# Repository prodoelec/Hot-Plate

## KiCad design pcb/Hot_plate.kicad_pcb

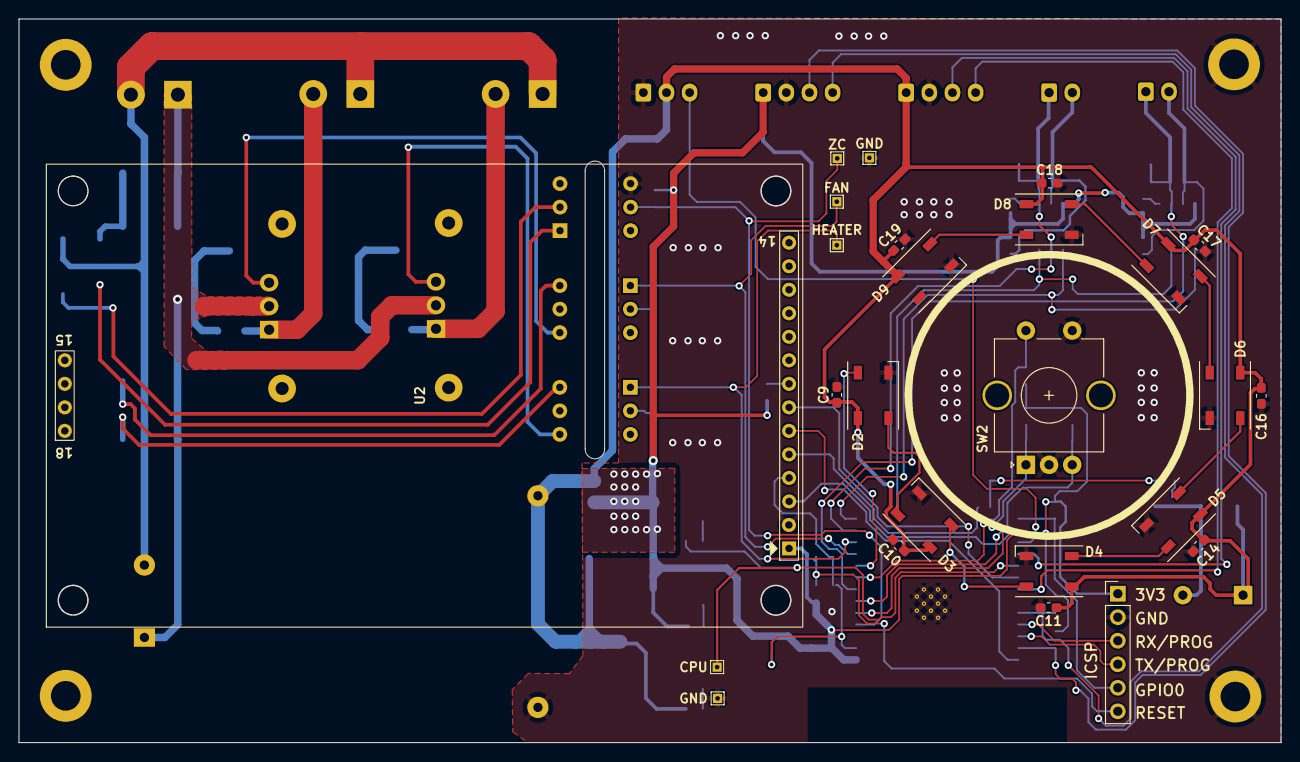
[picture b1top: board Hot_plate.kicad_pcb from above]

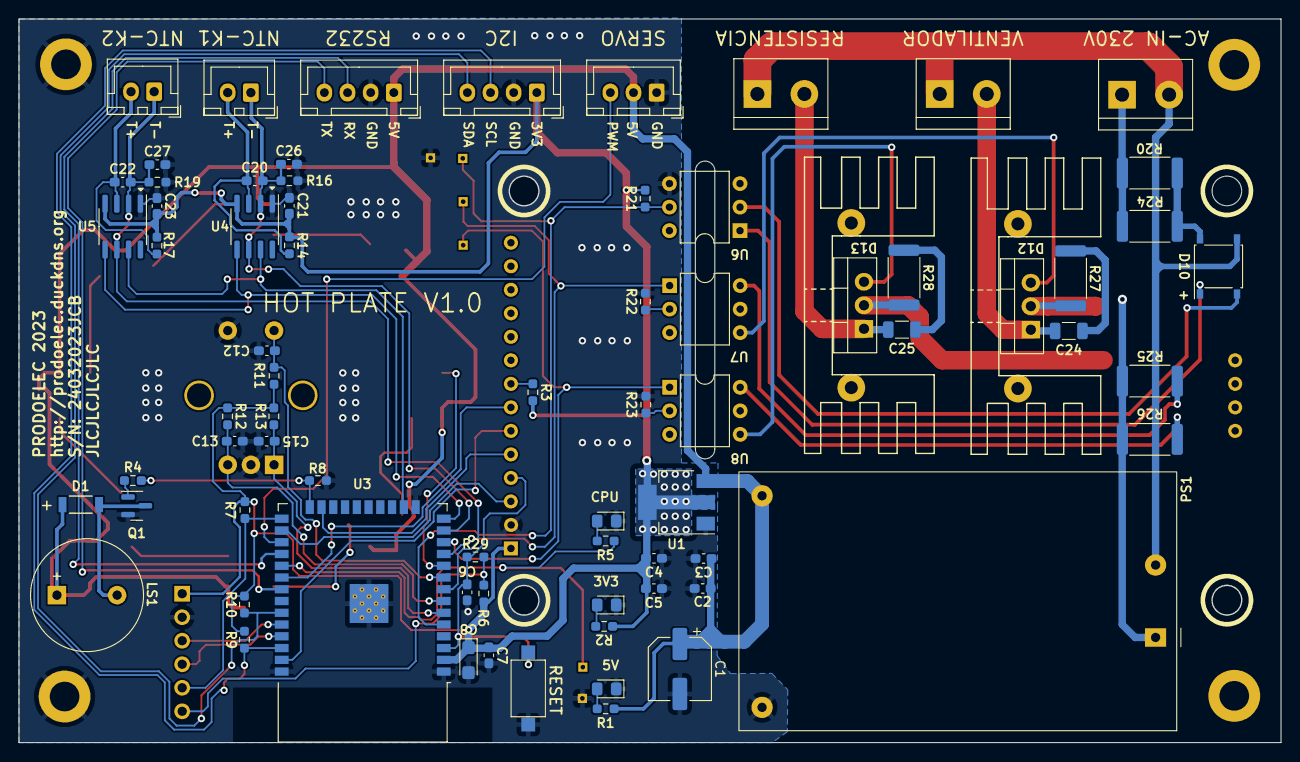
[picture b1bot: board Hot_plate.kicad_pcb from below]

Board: 2 copper layers, 136.3 x 78.1 mm, 103 parts (74 on the bottom side), 60 nets.

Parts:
C1: 220uF/16V; CP_Elec_6.3x7.7
C2, C5: 100nF/25V; C_0603_1608Metric_Pad1.08x0.95mm_HandSolder
C3, C4: 10uF/25V; C_0603_1608Metric_Pad1.08x0.95mm_HandSolder
C6, C7, C9, C10, C11, C12, C13, C14, C15, C16, C17, C18, C19, C20, C21, C22, C23, C26, C27: 100nF; C_0603_1608Metric_Pad1.08x0.95mm_HandSolder
C8: 100uF/10V; CP_EIA-3216-10_Kemet-I
C24, C25: 10nF/400V; C_1206_3216Metric
D1: BAS85-115; DIODE_BAS85_115-M
D2, D3, D4, D5, D6, D7, D8, D9: WS2812B; LED_WS2812B_PLCC4_5.0x5.0mm_P3.2mm
D10: ABS8; Diode_Bridge_Diotec_ABS
D12, D13: BTB10-800CWRG; TO-220-3_Vertical
H1, H3: MountingHole; MountingHole_3.2mm_M3_DIN965_Pad
H2, H4: MountingHole_Pad; MountingHole_3.2mm_M3_DIN965_Pad
HS1, HS2: Heatsink_Pad; Heatsink_Stonecold_HS-132_32x14mm_2xFixation1.5mm
J1: IN-AC; TerminalBlock_bornier-2_P5.08mm
J2: ISCP; PinHeader_1x06_P2.54mm_Vertical
J3: PANTALLA NEXTION; JST_XH_B4B-XH-A_1x04_P2.50mm_Vertical
J4: SERVO; JST_XH_B3B-XH-A_1x03_P2.50mm_Vertical
J5: I2C; JST_XH_B4B-XH-A_1x04_P2.50mm_Vertical
J6: SONDA 1; JST_XH_B2B-XH-A_1x02_P2.50mm_Vertical
J7: SONDA 2; JST_XH_B2B-XH-A_1x02_P2.50mm_Vertical
J8: VENTILADOR; TerminalBlock_bornier-2_P5.08mm
J9: RESISTENCIA; TerminalBlock_bornier-2_P5.08mm
LD1: 5V; LED_0805_2012Metric_Pad1.15x1.40mm_HandSolder
LD2: 3V3; LED_0805_2012Metric_Pad1.15x1.40mm_HandSolder
LD3: CPU; LED_0805_2012Metric_Pad1.15x1.40mm_HandSolder
LS1: PKMCS0909E4000-R1; Buzzer_12x9.5RM6.5
PS1: HLK-10M05; Converter_ACDC_HiLink_HLK-10Mxx
Q1: BC847; SOT-23
R1: 4K7; R_0603_1608Metric_Pad0.98x0.95mm_HandSolder
R2, R5, R29: 470; R_0603_1608Metric_Pad0.98x0.95mm_HandSolder
R3: 0; R_0603_1608Metric_Pad0.98x0.95mm_HandSolder
R4: 1K; R_0603_1608Metric_Pad0.98x0.95mm_HandSolder
R6, R7, R8, R9, R10, R11, R12, R13, R21: 10K; R_0603_1608Metric_Pad0.98x0.95mm_HandSolder
R14, R17: 0 *; R_0603_1608Metric_Pad0.98x0.95mm_HandSolder
R16, R19: 100K; R_0603_1608Metric_Pad0.98x0.95mm_HandSolder
R20, R24: 120K; R_2512_6332Metric
R22, R23: 220; R_0603_1608Metric_Pad0.98x0.95mm_HandSolder
R25, R26: 1K; R_2512_6332Metric
R27, R28: 39 *; R_2512_6332Metric
SW1: RESET; SW_SPST_CK_RS282G05A3
SW2: RotaryEncoder_Switch; RotaryEncoder_Alps_EC11E-Switch_Vertical_H20mm_CircularMoun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
TP1: HEATER; TestPoint_THTPad_1.0x1.0mm_Drill0.5mm
TP2: FAN; TestPoint_THTPad_1.0x1.0mm_Drill0.5mm
TP3: ZC; TestPoint_THTPad_1.0x1.0mm_Drill0.5mm
TP4, TP6: GND; TestPoint_THTPad_1.0x1.0mm_Drill0.5mm
TP5: CPU; TestPoint_THTPad_1.0x1.0mm_Drill0.5mm
U1: LD1117S33TR_SOT223; SOT-223-3_TabPin2
U2: ILI9341
U3: ESP32-WROOM-32
U4, U5: MAX6675; SOIC-8_3.9x4.9mm_P1.27mm
U6: 4N25; DIP-6_W7.62mm
U7, U8: MOC3021M; DIP-6_W7.62mm

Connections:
+3V3: C4.1, C5.1, C7.1, C8.1, C21.2, C23.2, J2.1, J5.1, R2.1, R3.2, R6.1, R7.2, R9.2, R10.2, R11.2, R12.2, R13.2, R14.2, R17.2, R21.2, U1.2 (VO), U2.1 (3V3), U3.2 (VDD), U4.4 (VCC), U5.4 (VCC)
+5V: C1.1, C2.1, C3.1, C9.1, C10.1, C11.1, C14.1, C16.1, C17.1, C18.1, C19.1, D1.1 (K), D2.1 (VDD), D3.1 (VDD), D4.1 (VDD), D5.1 (VDD), D6.1 (VDD), D7.1 (VDD), D8.1 (VDD), D9.1 (VDD), J3.1, J4.2, LS1.1, PS1.4 (+Vout), R1.1, U1.3 (VI)
BUZZER: R4.2, R8.2, U3.24 (IO2)
CK_ENC: C13.1, R12.1, SW2.B, U3.7 (IO35)
DT_ENC: C15.1, R13.1, SW2.A, U3.6 (IO34)
GND: C1.2, C2.2, C3.2, C4.2, C5.2, C6.2, C7.2, C8.2, C9.2, C10.2, C11.2, C12.2, C13.2, C14.2, C15.2, C16.2, C17.2, C18.2, C19.2, C21.1, C23.1, C26.2, C27.2, D2.3 (VSS), D3.3 (VSS), D4.3 (VSS), D5.3 (VSS), D6.3 (VSS), D7.3 (VSS), D8.3 (VSS), D9.3 (VSS), H2.1, H4.1, J2.2, J3.2, J4.1, J5.2, LD1.1 (K), LD2.1 (K), LD3.1 (K), PS1.3 (-Vout), Q1.2 (E), R8.1, R16.1, R19.1, R22.1, R23.1, SW1.1, SW2.C, SW2.S1, TP4.1, TP6.1, U1.1 (GND), U2.2 (GND), U3.1 (GND), U3.15 (GND), U3.38 (GND), U3.39 (GND), U4.1 (GND), U5.1 (GND), U6.4
GPIO0: J2.5, R7.1, U3.25 (IO0)
LED_CPU: R5.1, TP5.1, U3.29 (IO5)
LED_ENC: D2.4 (DIN), U3.10 (IO25)
LINE: D12.2 (A2), D13.2 (A2), J1.1, PS1.1 (AC/L), R20.2, R24.2, R25.2, R26.2, R27.2, R28.2
MAX_CS1/NTC1: C20.2, C26.1, J6.1, R16.2, U3.13 (IO14), U4.2 (T-), U4.6 (~CS)
MAX_CS2/NTC2: C22.2, C27.1, J7.1, R19.2, U3.8 (IO32), U5.2 (T-), U5.6 (~CS)
MAX_SCK: U3.14 (IO12), U4.5 (SCK), U5.5 (SCK)
MAX_SO: U3.16 (IO13), U4.7 (SO), U5.7 (SO)
MOSI: U2.6 (MOSI), U3.37 (IO23)
NEUT: D10.3, J1.2, J8.1, J9.1, PS1.2 (AC/N)
unnamed: C24.1, R27.1
unnamed: C25.1, R28.1
unnamed: D1.2 (A), LS1.2, Q1.3 (C)
unnamed: D2.2 (DOUT), D3.4 (DIN)
unnamed: D3.2 (DOUT), D4.4 (DIN)
unnamed: D4.2 (DOUT), D5.4 (DIN)
unnamed: D5.2 (DOUT), D6.4 (DIN)
unnamed: D6.2 (DOUT), D7.4 (DIN)
unnamed: D7.2 (DOUT), D8.4 (DIN)
unnamed: D8.2 (DOUT), D9.4 (DIN)
unnamed: D10.1 (+), U6.1
unnamed: D10.2 (-), U6.2
unnamed: D10.4, R20.1, R24.1
unnamed: C24.2, D12.1 (A1), J8.2
unnamed: D12.3 (G), U7.4
unnamed: C25.2, D13.1 (A1), J9.2
unnamed: D13.3 (G), U8.4
unnamed: C20.1, J6.2, R14.1, U4.3 (T+)
unnamed: C22.1, J7.2, R17.1, U5.3 (T+)
unnamed: LD1.2 (A), R1.2
unnamed: LD2.2 (A), R2.2
unnamed: LD3.2 (A), R5.2
unnamed: Q1.1 (B), R4.1
unnamed: R22.2, U7.2
unnamed: R23.2, U8.2
unnamed: R25.1, U7.6
unnamed: R26.1, U8.6
unnamed: R3.1, U2.8 (LED)
PWM/SERVO: J4.3, U3.27 (IO16)
RST_ESP: C6.1, R29.2, SW1.2, U2.4 (RESET), U3.3 (EN)
RST_PROG: J2.6, R6.2, R29.1
RX_232: J3.3, U3.28 (IO17)
RX_PROG: J2.3, U3.34 (RXD0/IO3)
SCK: U2.7 (SCK), U3.30 (IO18)
SCL: J5.3, R9.1, U3.36 (IO22)
SDA: J5.4, R10.1, U3.33 (IO21)
SSR_FAN: TP2.1, U3.11 (IO26), U7.1
SSR_HEATER: TP1.1, U3.12 (IO27), U8.1
SW_ENC: C12.1, R11.1, SW2.S2, U3.9 (IO33)
TFT_CS: U2.3 (TFT_CS), U3.26 (IO4)
TFT_DC: U2.5 (TFT_DC), U3.23 (IO15)
TX_232: J3.4, U3.31 (IO19)
TX_PROG: J2.4, U3.35 (TXD0/IO1)
ZERO_C: R21.1, TP3.1, U3.5 (SENSOR_VN), U6.5

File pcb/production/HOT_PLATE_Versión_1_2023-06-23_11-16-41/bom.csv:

Designator,Footprint,Quantity,Value,LCSC Part #
C1,CP_Elec_8x6.9,1,220uF/10V,
"C10, C11, C12, C13, C14, C15, C16, C17, C18, C19, C20, C21, C22, C23, C6, C7, C9",0603,17,100nF,
"C2, C5",0603,2,100nF/25V,
"C24, C25",1206,2,10nF/400V,
"C3, C4",0603,2,10uF/25V,
C8,CP_EIA-3216-10_Kemet-I,1,100uF/10V,
D1,DIODE_BAS85_115-M,1,BAS85-115,
D10,Diode_Bridge_Diotec_ABS,1,ABS8,
"D12, D13",TO-220-3_Vertical,2,BTB10-800CWRG,
"D2, D3, D4, D5, D6, D7, D8, D9",LED_WS2812B_PLCC4_5.0x5.0mm_P3.2mm,8,WS2812B,
"H1, H3",MountingHole_3.2mm_M3_DIN965_Pad,2,MountingHole,
"H2, H4",MountingHole_3.2mm_M3_DIN965_Pad,2,MountingHole_Pad,
"HS1, HS2",Heatsink_Stonecold_HS-132_32x14mm_2xFixation1.5mm,2,Heatsink_Pad,
J1,TerminalBlock_bornier-2_P5.08mm,1,IN-AC,
J2,PinHeader_1x06_P2.54mm_Vertical,1,ISCP,
J3,JST_XH_B4B-XH-A_1x04_P2.50mm_Vertical,1,PANTALLA NEXTION,
J4,JST_XH_B3B-XH-A_1x03_P2.50mm_Vertical,1,SERVO,
J5,JST_XH_B4B-XH-A_1x04_P2.50mm_Vertical,1,I2C,
J6,JST_XH_B2B-XH-A_1x02_P2.50mm_Vertical,1,SONDA 1,
J7,JST_XH_B2B-XH-A_1x02_P2.50mm_Vertical,1,SONDA 2,
J8,TerminalBlock_bornier-2_P5.08mm,1,VENTILADOR,
J9,TerminalBlock_bornier-2_P5.08mm,1,RESISTENCIA,
LD1,0805,1,5V,
LD2,0805,1,3V3,
LD3,0805,1,CPU,
LS1,Buzzer_12x9.5RM6.5,1,PKMCS0909E4000-R1,
PS1,Converter_ACDC_HiLink_HLK-10Mxx,1,HLK-10M05,
Q1,SOT-23,1,BC847,
"R1, R2, R4, R5",0603,4,1K,
"R10, R11, R12, R13, R21, R6, R7, R8, R9",0603,9,10K,
"R14, R17",0603,2,100k,
"R15, R16, R18, R19",0603,4,0 *,
"R20, R24",2512,2,120K,
"R22, R23",0603,2,220,
"R25, R26",2512,2,1K,
"R27, R28",2512,2,39 *,
R29,0603,1,470,
R3,0603,1,0,
SW1,SW_SPST_CK_RS282G05A3,1,RESET,
SW2,RotaryEncoder_Alps_EC11E-Switch_Vertical_H20mm_CircularMountingHoles,1,RotaryEncoder_Switch,
TP1,TestPoint_THTPad_1.0x1.0mm_Drill0.5mm,1,HEATER,
TP2,TestPoint_THTPad_1.0x1.0mm_Drill0.5mm,1,FAN,
TP3,TestPoint_THTPad_1.0x1.0mm_Drill0.5mm,1,ZC,
"TP4, TP6",TestPoint_THTPad_1.0x1.0mm_Drill0.5mm,2,GND,
TP5,TestPoint_THTPad_1.0x1.0mm_Drill0.5mm,1,CPU,
U1,SOT-223-3_TabPin2,1,LD1117S33TR_SOT223,
U2,ILI9341,1,ILI9341,
U3,ESP32-WROOM-32,1,ESP32-WROOM-32,
"U4, U5",SOIC-8_3.9x4.9mm_P1.27mm,2,MAX6675,
U6,DIP-6_W7.62mm,1,4N25,
"U7, U8",DIP-6_W7.62mm,2,MOC3021M,

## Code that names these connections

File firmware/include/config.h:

// !!!!!! En la libreria del TFT hay que configurar los pines e invcertir los colores en el fichero User_Setup.h
// #define ILI9341_2_DRIVER     // Alternative ILI9341 driver, see https://github.com/Bodmer/TFT_eSPI/issues/1172 ( descomentar )
// comentar estas
// #define TFT_CS   PIN_D8  // Chip select control pin D8
// #define TFT_DC   PIN_D3  // Data Command control pin
// #define TFT_RST  PIN_D4  // Reset pin (could connect to NodeMCU RST, see next line)
// ###### EDIT THE PIN NUMBERS IN THE LINES FOLLOWING TO SUIT YOUR ESP32 SETUP   ######
// For ESP32 Dev board (only tested with ILI9341 display)
// The hardware SPI can be mapped to any pins
// #define TFT_MISO 19 ( no es necesaria )
// #define TFT_MOSI 23
// #define TFT_SCLK 18
// #define TFT_CS    4  // Chip select control pin
// #define TFT_DC   15  // Data Command control pin
// #define TFT_RST   4  // Reset pin (could connect to RST pin) Comentar esta línea
// #define TFT_RST  -1  // Set TFT_RST to -1 if display RESET is connected to ESP32 board RST
// If colours are inverted (white shows as black) then uncomment one of the next
// 2 lines try both options, one of the options should correct the inversion.
// #define TFT_INVERSION_ON ( descomentar )

#include <SPI.h>
#include <Wire.h>
#include <max6675.h>
#include <TFT_eSPI.h>
#include <Adafruit_NeoPixel.h>
#include <iconos.h>

/*******************************************************************************
  Ajustes fases de reflow.
  En función del dispositivo descomentar las que correspondan a este.
*******************************************************************************/
// HOT-PLATE
#define READY    {"READY",TFT_WHITE,25.0,0,255,255,255,0,0}
#define PREHEAT  {"PRE-HEAT",TFT_GREENYELLOW,125.0,90.0,153,153,0,1.0}
#define SOAK     {"SOAK",TFT_ORANGE,180.0,90.0,204,102,0,1.8}
#define REFLOW   {"REFLOW",TFT_RED,210.0,30.0,255,0,0,14.0}
#define COOLING  {"COOLING",TFT_BLUE,180.0,30.0,0,0,255,0,2.5}
#define DONE     {"DONE",TFT_GREEN,0,0,0,255,0,0,0}

// OVEN
// #define READY   {"READY",TFT_WHITE,25.0,0,255,255,255,0,0}
// #define PREHEAT {"PRE-HEAT",TFT_GREENYELLOW,125.0,90.0,153,153,0,16.0}
// #define SOAK    {"SOAK",TFT_ORANGE,180.0,90.0,204,102,0,14.0}
// #define REFLOW  {"REFLOW",TFT_RED,210.0,30.0,255,0,0,20.0}
// #define COOLING {"COOLING",TFT_BLUE,180.0,30.0,0,0,255,0,2.5}
// #define DONE    {"DONE",TFT_GREEN,0,0,0,255,0,0,0}

// Definiciones genericas
#define TEMPERATURA_SEGURA    50
#define NUM_LEDS_ENCODER      8

// Carga las fuentes a utilizar
#define FONT2 2
#define FONT4 4
#define FONT6 6
#define FONT7 7
#define FONT8 8

// Definiciones pines MAX6675-1 MAX6675-2
#define MAX_SCK     12    // Reloj Max6675
#define MAX_SO      13    // Salida de datos MAX6675
#define MAX_CS1     14    // Seleccion MAX6675-1
#define MAX_CS2     32    // Seleccion MAX6675-2
#define TIME_SAMPLE 1000  // Tiempo de lectura temperatura cada 1s


// Definiciones encoder
#define CK_ENCODER  35    // Señal reloj encoder
#define DT_ENCODER  34    // Señal de datos encoder
#define SW_ENCODER  33    // Pulsador encoder
#define DELAY_CK    20    // Retardo giro encoder
#define DELAY_SW    300   // Retardo pulsador encoder

// Definiciones salidas y entradas
#define BUZZER        2   // Control zumbador
#define SSR           27  // Rele estado solido resistencia
#define FAN           26  // Rele estado solido ventilador
#define LED_ENCODER   25  // Tira led WS2812 encoder
#define ZERO_CROSSING 39  // Paso por cero AC
#define LED_CPU       5   // Led CPU

// Definiciones puerto serie (Pantalla Nextion)
#define RX_232        17  // Recepción RS-232 
#define TX_232        19  // Transmisión RS-232 

// Definiciones PWM BUZZER
#define PWM_BUZZER_CHANNEL    0     // Canal PWM asigado a buzzer
#define PWM_BUZZER_FREQUENCY  10000 // Frecuencia del canal Hz
#define PWM_BUZZER_RESOLUTION 8     // Resolucion canal

// Definiciones PWM SSR
#define PWM_SSR_CHANNEL       2     // Canal PWM asignado a SSR
#define PWM_SSR_FREQUENCY     5     // Frecuencia del canal Hz
#define PWM_SSR_RESOLUTION    8     // Resolucion del canal

// Definiciones PWM FAN
#define PWM_FAN_CHANNEL       4     // Canal PWM asignado a SSR
#define PWM_FAN_FREQUENCY     10    // Frecuencia del canal Hz
#define PWM_FAN_RESOLUTION    8     // Resolucion del canal

struct menus
{
    String       nombre;
    unsigned int pos_x;
    unsigned int pos_y;
};

struct fases
{   
    String nombre;          // Nombre a mostrar en pantalla
    int    color;           // Color del texto en pantalla
    float  temperatura;     // Temperatura de consigna
    float  tiempo;          // Tiempo para conseguir la temperatura
    int    R;               // Valor rojo led
    int    G;               // Valor verde led
    int    B;               // Valor azul led
    float  k_pwm;           // Constante K PWM SSR
    float  k_fan;           // Constante K PWM FAN
};


// Crea objeto pantalla TFT
TFT_eSPI tft = TFT_eSPI();    // TFT

// Crea objetos termopares 
MAX6675 termopar1;            // MAX6675-1
MAX6675 termopar2;            // MAX6675-2

// Crea objeto tira de led WS2812 Encoder
Adafruit_NeoPixel leds = Adafruit_NeoPixel(NUM_LEDS_ENCODER, LED_ENCODER, NEO_GRB + NEO_KHZ800); // Led WS2812B
 
menus menu[4];

fases fase[6];

// Define variables globales
float   temperatura;                // Temperatura de horno / hot-plate
float   temperatura_2;
int     pwm_ssr            = 0;     // Valor de 0-100% del PWM resistencia
int     pwm_fan            = 0;     // Valor de 0-100% del PWM ventilador
int     posActualEncoder   = 0;     // Posición actual encoder
int     posFinalEncoder    = 7;    // Posición maxima encoder

bool  estadoPulsador     = false;  // Estado pulsador encoder
bool  error              = false;  // Error sonda temperatura
bool  estadoHorno        = false;  // Estado horno

long  zero;

float tempConsigna       = 25.0;  // Temperatura de consigna inicial
float incrementoTemp     = 0;     // Incremento de temperatura         


  int progreso,_progreso;

// // Define variables NTC para calcular la temperatura
// int Vo;
// float R1 = 100000;              // resistencia fija del divisor de tension 
// float logR2, R2, tempNTC;
// float c1 = 2.114990448e-03, c2 = 0.3832381228e-04, c3 = 5.228061052e-07;
// // coeficientes de S-H en pagina: 
// // http://www.thinksrs.com/downloads/programs/Therm%20Calc/NTCCalibrator/NTCcalculator.htm
